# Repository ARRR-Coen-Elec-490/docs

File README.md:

# Documentation Repository

## Table of Contents <!-- omit in toc -->

- [Documentation Repository](#documentation-repository)
    - [Introduction](#introduction)
    - [Repository Structure](#repository-structure)
    - [System Architecture Documentation](#system-architecture-documentation)
    - [Hardware Documentation](#hardware-documentation)
    - [Software Documentation](#software-documentation)
    - [AI Usage Claim](#ai-usage-claim)

## Introduction

This repository serves as the Single Source of Truth (*SSOT*) for Team #23's fulfillment of the COEN/ELEC 490 2026-2027 Capstone Session.  Within this repository, one can find documentation related to every single part of this project, including hardware, software, architecture, and procurement documents.  The documentation found in this repository is updated and maintained regularly to ensure it follows all the appropriate IEEE, IEC, and ISO standards, according to each standards relevancy and availability.

## Repository Structure

```text
docs/
 ┣ ai-usage/                    # AI Prompting Templates and Logs (Empty)
 ┣ hardware-documentation/      # PCB & BOM Documents
 ┃ ┣ abtrs_torso/               # KiCAD PCB, Schematics, and Simulations
 ┃ ┣ abtrs_torso_information/   # PCB Support Documents
 ┃ ┣ bom/                       # Bill of Materials
 ┃ ┣ datasheets/                # Datasheets for all thirs-party components
 ┃ ┣ schematics/                # Auto-Generated Printables
 ┃ ┗ wiring-diagrams/           # System-Level Wiring Information
 ┣ software-documentation/      # Software Business Logic Documents
 ┣ system-architecture/         # Overarching System Architecture Documents
 ┗ user-manuals/                # Operation and Maintenance Documents (Empty)
```

## System Architecture Documentation

The ```system-architecture``` folder contains the black-box and white-box representations of the system, including the interactions betwen the hardware and software layers.  In addition, this folder contains diagrams related to the system operation including flowcharts, activity/sequence diagrams, and entity relationship diagrams.

## Hardware Documentation

The ```hardware-documentation``` folder contains all information related to the PCB and BOM.  Regarding the PCB, schematics, 3D Models, and simulations have been created to demonstrate the design and validation of the board needed for our project.  According to this PCB, a detailed and through BOM was ceated to hold all the components needed for the product being developed.  Furthermore, other 3D models, wiring diagrams, and support documents have been included to illustrate the complete hardware design of this project.

## Software Documentation

The ```software-documentation``` folder contains all the documents related to the various software sub-layers noted in white-box system architecture diagrams.  The contents of this folder expand each layer, providing detailed representations of any software business logic employed in this project.  A combination of flowcharts, activity/sequence diagrams, entity relationship diagrams, and class diagrams can be found for the different layers of the software architecture, to ensure the full illustration of the scope and responsibilities attributed to each software process found in the system.

## AI Usage Claim

In accordance with the policies put forth by both Concordia University and the COEN/ELEC 490 Capstone Committe, AI cannot be used to design or implement any aspects of the capstone project being developed by this team.  Instead, AI may only be used to enhance research or problem-solving processes across the team.  In other words, AI can be leveraged to enhance the toolsets employed by this team, but can in no way directly contribute to the final product of this project.  Failure to comply with these policies will result in grave penalties.  As such, to prevent such a scenario, the ```ai-usage``` folder has been created to contain any and all prompts used throughout the develoment of this project, and will serve as the team's method to demonstrate compliance with the policies discussed above.

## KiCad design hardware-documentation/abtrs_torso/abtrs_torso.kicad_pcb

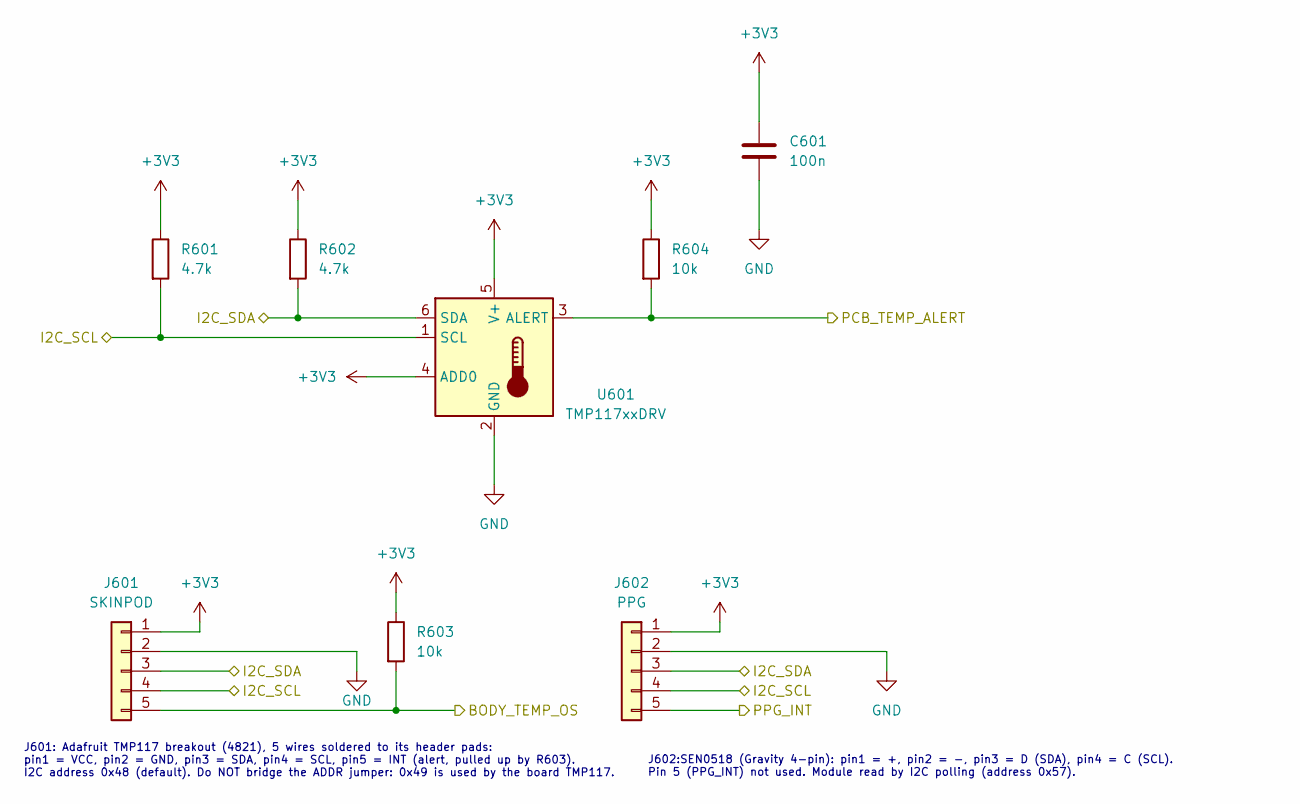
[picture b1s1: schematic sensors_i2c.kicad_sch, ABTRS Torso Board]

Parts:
C601: 100n; C_0603_1608Metric; MPN C0603C104K5RACTU
J601: SKINPOD; JST_PH_S5B-PH-K_1x05_P2.00mm_Horizontal; MPN S5B-PH-K-S
J602: PPG; JST_PH_S5B-PH-K_1x05_P2.00mm_Horizontal; MPN S5B-PH-K-S
R601, R602: 4.7k; R_0603_1608Metric; MPN RC0603FR-074K7L
R603, R604: 10k; R_0603_1608Metric; MPN RC0603FR-0710KL
U601: TMP117xxDRV; WSON-6-1EP_2x2mm_P0.65mm_EP1x1.6mm; MPN TMP117AIDRVR

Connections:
+3V3: C601.1, J601.1, J602.1, R601.1, R602.1, R603.1, R604.1, U601.4 (ADD0), U601.5 (V+); also elsewhere on the board
/BODY_TEMP_OS: J601.5, R603.2; also elsewhere on the board
/I2C_SCL: J601.4, J602.4, R601.2, U601.1 (SCL); also elsewhere on the board
/I2C_SDA: J601.3, J602.3, R602.2, U601.6 (SDA); also elsewhere on the board
/PCB_TEMP_ALERT: R604.2, U601.3 (ALERT); also elsewhere on the board
/PPG_INT: J602.5; also elsewhere on the board
GND: C601.2, J601.2, J602.2, U601.2 (GND); also elsewhere on the board

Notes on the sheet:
J602:SEN0518 (Gravity 4-pin): pin1 = +, pin2 = -, pin3 = D (SDA), pin4 = C (SCL). Pin 5 (PPG_INT) not used. Module read by I2C polling (address 0x57).
J601: Adafruit TMP117 breakout (4821), 5 wires soldered to its header pads: pin1 = VCC, pin2 = GND, pin3 = SDA, pin4 = SCL, pin5 = INT (alert, pulled up by R603). I2C address 0x48 (default). Do NOT bridge the ADDR jumper: 0x49 is used by the board TMP117.

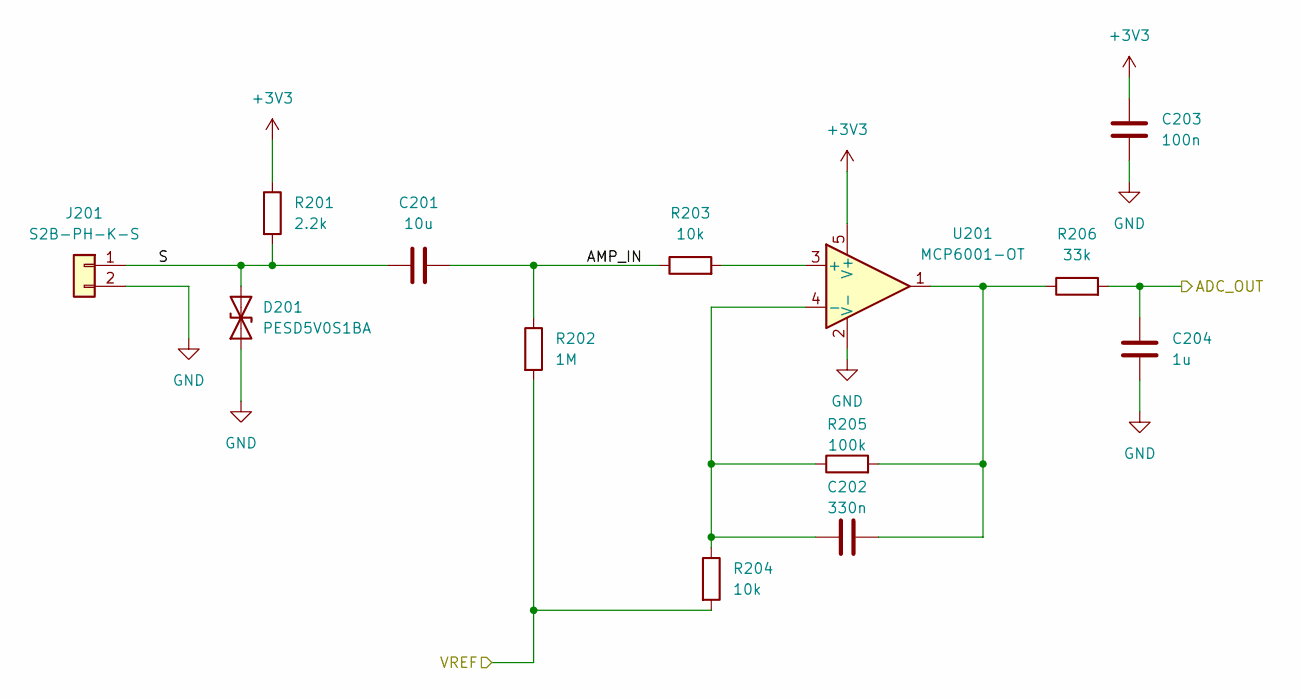
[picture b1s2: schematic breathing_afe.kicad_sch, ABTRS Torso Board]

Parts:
C201: 10u; C_0603_1608Metric; MPN CL10A106KP8NNNC
C202: 330n; C_0603_1608Metric; MPN CL10B334KO8NNNC
C203: 100n; C_0603_1608Metric; MPN C0603C104K5RACTU
C204: 1u; C_0603_1608Metric; MPN CC0603KPX5R9BB105
D201: PESD5V0S1BA; D_SOD-323; MPN PESD5V0S1BA,115
J201: S2B-PH-K-S; JST_PH_S2B-PH-K_1x02_P2.00mm_Horizontal; MPN S2B-PH-K-S
R201: 2.2k; R_0603_1608Metric; MPN AC0603FR-072K2L
R202: 1M; R_0603_1608Metric; MPN RC0603FR-071ML
R203, R204: 10k; R_0603_1608Metric; MPN RC0603FR-0710KL
R205: 100k; R_0603_1608Metric; MPN AC0603FR-07100KL
R206: 33k; R_0603_1608Metric; MPN RC0603FR-0733KL
U201: MCP6001-OT; SOT-23-5; MPN MCP6001T-I/OT

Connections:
+3V3: C203.1, R201.1, U201.5 (V+); also elsewhere on the board
/CHEST/AMP_IN: C201.2, R202.1, R203.1
/CHEST/S: C201.1, D201.2 (A2), J201.1, R201.2
/CHEST_ADC: C204.1, R206.2; also elsewhere on the board
/VREF: R202.2, R204.2; also elsewhere on the board
GND: C203.2, C204.2, D201.1 (A1), J201.2, U201.2 (V-); also elsewhere on the board
unnamed: C202.2, R205.2, R206.1, U201.1
unnamed: R203.2, U201.3 (+)
unnamed: C202.1, R204.1, R205.1, U201.4 (-)

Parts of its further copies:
C301: 10u; C_0603_1608Metric; MPN CL10A106KP8NNNC
C302: 330n; C_0603_1608Metric; MPN CL10B334KO8NNNC
C303: 100n; C_0603_1608Metric; MPN C0603C104K5RACTU
C304: 1u; C_0603_1608Metric; MPN CC0603KPX5R9BB105
D301: PESD5V0S1BA; D_SOD-323; MPN PESD5V0S1BA,115
J301: S2B-PH-K-S; JST_PH_S2B-PH-K_1x02_P2.00mm_Horizontal; MPN S2B-PH-K-S
R301: 2.2k; R_0603_1608Metric; MPN AC0603FR-072K2L
R302: 1M; R_0603_1608Metric; MPN RC0603FR-071ML
R303, R304: 10k; R_0603_1608Metric; MPN RC0603FR-0710KL
R305: 100k; R_0603_1608Metric; MPN AC0603FR-07100KL
R306: 33k; R_0603_1608Metric; MPN RC0603FR-0733KL
U301: MCP6001-OT; SOT-23-5; MPN MCP6001T-I/OT

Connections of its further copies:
+3V3: C303.1, R301.1, U301.5 (V+); also elsewhere on the board
/ABD/AMP_IN: C301.2, R302.1, R303.1
/ABD/S: C301.1, D301.2 (A2), J301.1, R301.2
/ABD_ADC: C304.1, R306.2; also elsewhere on the board
/VREF: R302.2, R304.2; also elsewhere on the board
GND: C303.2, C304.2, D301.1 (A1), J301.2, U301.2 (V-); also elsewhere on the board
unnamed: C302.2, R305.2, R306.1, U301.1
unnamed: R303.2, U301.3 (+)
unnamed: C302.1, R304.1, R305.1, U301.4 (-)

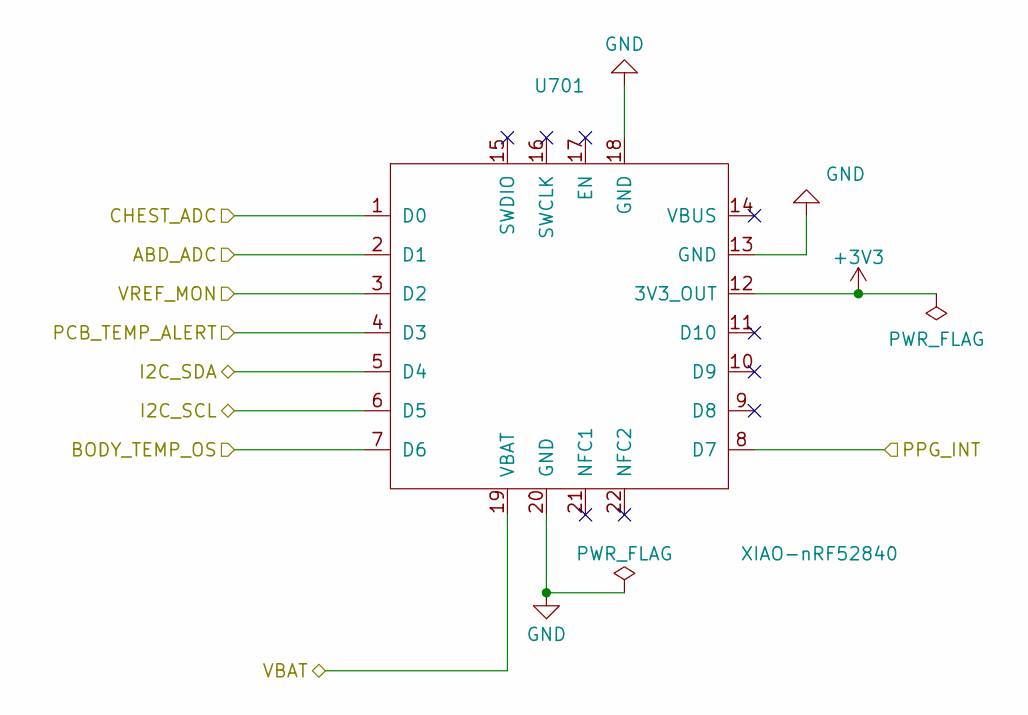
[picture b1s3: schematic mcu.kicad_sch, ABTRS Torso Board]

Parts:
U701: XIAO-nRF52840; XIAO-nRF52840-SMD; MPN 102010448

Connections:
+3V3: U701.12 (3V3_OUT); also elsewhere on the board
/ABD_ADC: U701.2 (D1); also elsewhere on the board
/BODY_TEMP_OS: U701.7 (D6); also elsewhere on the board
/CHEST_ADC: U701.1 (D0); also elsewhere on the board
/I2C_SCL: U701.6 (D5); also elsewhere on the board
/I2C_SDA: U701.5 (D4); also elsewhere on the board
/PCB_TEMP_ALERT: U701.4 (D3); also elsewhere on the board
/PPG_INT: U701.8 (D7); also elsewhere on the board
/VBAT: U701.19 (VBAT); also elsewhere on the board
/VREF: U701.3 (D2); also elsewhere on the board
GND: U701.13 (GND), U701.18 (GND), U701.20 (GND); also elsewhere on the board

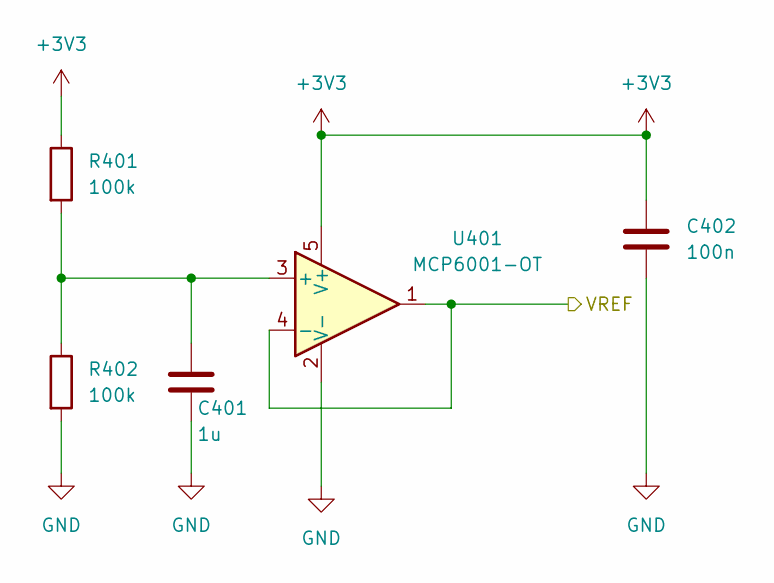
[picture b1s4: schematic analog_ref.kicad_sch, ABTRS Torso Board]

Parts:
C401: 1u; C_0603_1608Metric; MPN CC0603KPX5R9BB105
C402: 100n; C_0603_1608Metric; MPN C0603C104K5RACTU
R401, R402: 100k; R_0603_1608Metric; MPN AC0603FR-07100KL
U401: MCP6001-OT; SOT-23-5; MPN MCP6001T-I/OT

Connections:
+3V3: C402.1, R401.1, U401.5 (V+); also elsewhere on the board
/VREF: U401.1, U401.4 (-); also elsewhere on the board
GND: C401.2, C402.2, R402.2, U401.2 (V-); also elsewhere on the board
unnamed: C401.1, R401.2, R402.1, U401.3 (+)

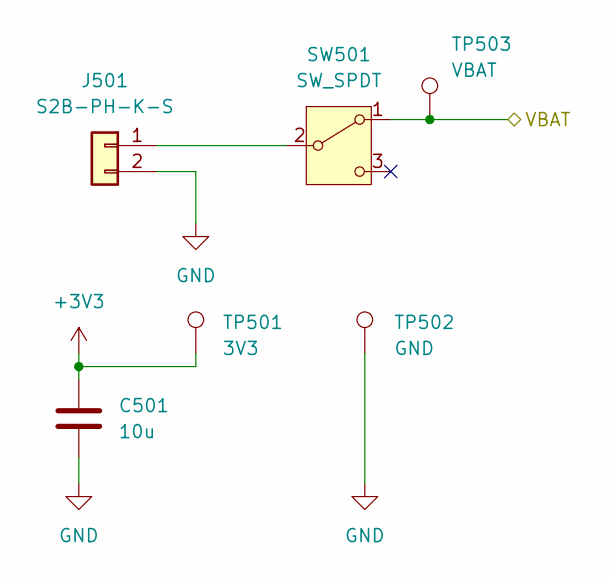
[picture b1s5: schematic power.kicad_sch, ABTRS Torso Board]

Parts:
C501: 10u; C_0603_1608Metric; MPN CL10A106KP8NNNC
J501: S2B-PH-K-S; JST_PH_S2B-PH-K_1x02_P2.00mm_Horizontal; MPN S2B-PH-K-S
SW501: SW_SPDT; SW_SPDT_CK_JS102011SAQN; MPN JS102011SAQN
TP501: 3V3; TestPoint_Pad_D1.5mm
TP502: GND; TestPoint_Pad_D1.5mm
TP503: VBAT; TestPoint_Pad_D1.5mm

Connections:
+3V3: C501.1, TP501.1 (1_1); also elsewhere on the board
/VBAT: SW501.1 (A), TP503.1 (1_1); also elsewhere on the board
GND: C501.2, J501.2, TP502.1 (1_1); also elsewhere on the board
unnamed: J501.1, SW501.2 (B)

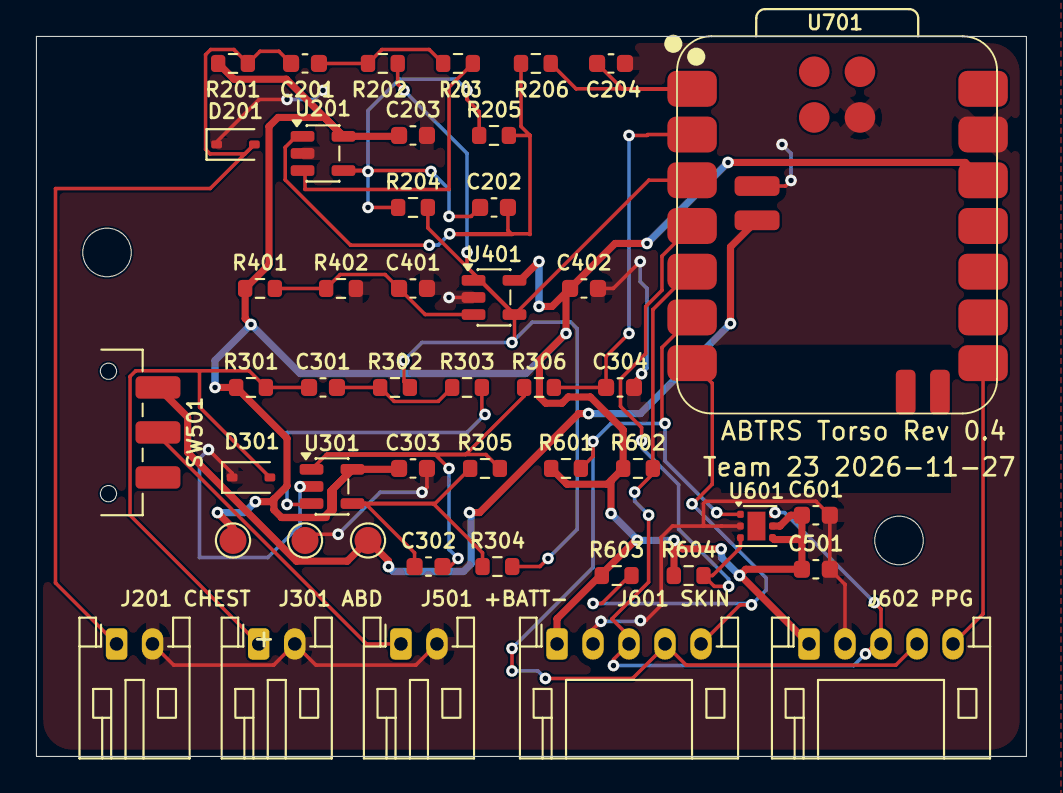
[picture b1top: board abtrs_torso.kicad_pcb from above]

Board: 2 copper layers, 55.0 x 40.0 mm, 48 parts (0 on the bottom side), 23 nets.

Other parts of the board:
H1, H2: MountingHole_2.7mm_M2.5

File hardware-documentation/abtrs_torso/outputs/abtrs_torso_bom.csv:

"Reference","Qty","Value","Footprint","Datasheet","#","Manufacturer","MPN","Supplier","Supplier P/N"
"SW501","1","SW_SPDT","Button_Switch_SMD:SW_SPDT_CK_JS102011SAQN","https://www.littelfuse.com/assetdocs/littelfuse-c-k-slide-js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","1","C&K","JS102011SAQN","DigiKey","401-1999-1-ND"
"C201,C301,C501","3","10u","Capacitor_SMD:C_0603_1608Metric","https://mm.digikey.com/Volume0/opasdata/d220001/medias/docus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","2","Samsung Electro-Mechanics","CL10A106KP8NNNC","DigiKey","1276-1192-1-ND"
"C202,C302","2","330n","Capacitor_SMD:C_0603_1608Metric","https://mm.digikey.com/Volume0/opasdata/d220001/medias/docus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","3","Samsung Electro-Mechanics","CL10B334KO8NNNC","DigiKey","1276-2048-1-ND"
"C203,C303,C402,C601","4","100n","Capacitor_SMD:C_0603_1608Metric","https://yageogroup.com/content/datasheet/asset/file/KEM_C100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","4","KEMET","C0603C104K5RACTU","DigiKey","399-C0603C104K5RACTUCT-ND"
"C204,C304,C401","3","1u","Capacitor_SMD:C_0603_1608Metric","https://yageogroup.com/content/datasheet/asset/file/UPY-GPHC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","5","Yageo","CC0603KPX5R9BB105","DigiKey","13-CC0603KPX5R9BB105CT-ND"
"J501","1","LiPo","Connector_JST:JST_PH_B2B-PH-K_1x02_P2.00mm_Vertical","https://www.jst-mfg.com/product/pdf/eng/ePH.pdf","6","JST","B2B-PH-K-S","DigiKey","455-1704-ND"
"J201,J301","2","Cord","Connector_JST:JST_PH_S2B-PH-K_1x02_P2.00mm_Horizontal","https://www.jst-mfg.com/product/pdf/eng/ePH.pdf","7","JST","S2B-PH-K-S","DigiKey","455-1719-ND"
"J601","1","SKINPOD","Connector_JST:JST_PH_S5B-PH-K_1x05_P2.00mm_Horizontal","https://www.jst-mfg.com/product/pdf/eng/ePH.pdf","8","JST","S5B-PH-K-S","DigiKey","455-1722-ND"
"J602","1","PPG","Connector_JST:JST_PH_S5B-PH-K_1x05_P2.00mm_Horizontal","https://www.jst-mfg.com/product/pdf/eng/ePH.pdf","9","JST","S5B-PH-K-S","DigiKey","455-1722-ND"
"D201,D301","2","PESD5V0S1BA","Diode_SMD:D_SOD-323","https://assets.nexperia.com/documents/data-sheet/PESD5V0S1BA.pdf","10","Nexperia","PESD5V0S1BA,115","DigiKey","1727-PESD5V0S1BA,115CT-ND"
"U601","1","TMP117xxDRV","Package_SON:WSON-6-1EP_2x2mm_P0.65mm_EP1x1.6mm","https://www.ti.com/lit/ds/symlink/tmp117.pdf","11","Texas Instruments","TMP117AIDRVR","DigiKey","296-51834-1-ND"
"U201,U301,U401","3","MCP6001-OT","Package_TO_SOT_SMD:SOT-23-5","https://ww1.microchip.com/downloads/en/DeviceDoc/MCP6001-1R-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","12","Microchip Technology","MCP6001T-I/OT","DigiKey","MCP6001T-I/OTCT-ND"
"R201,R301","2","2.2k","Resistor_SMD:R_0603_1608Metric","https://yageogroup.com/content/datasheet/asset/file/PYU-AC_5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","13","Yageo","AC0603FR-072K2L","DigiKey","311-2.2KLDCT-ND"
"R202,R302","2","1M","Resistor_SMD:R_0603_1608Metric","https://yageogroup.com/content/datasheet/asset/file/PYU-RC_G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","14","Yageo","RC0603FR-071ML","DigiKey","311-1.00MHRCT-ND"
"R203,R204,R303,R304,R603,R604","6","10k","Resistor_SMD:R_0603_1608Metric","https://yageogroup.com/content/datasheet/asset/file/PYU-RC_G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","15","Yageo","RC0603FR-0710KL","DigiKey","311-10.0KHRCT-ND"
"R205,R305,R401,R402","4","100k","Resistor_SMD:R_0603_1608Metric","https://yageogroup.com/content/datasheet/asset/file/PYU-AC_5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","16","Yageo","AC0603FR-07100KL","DigiKey","311-100KLDCT-ND"
"R206,R306","2","33k","Resistor_SMD:R_0603_1608Metric","https://yageogroup.com/content/datasheet/asset/file/PYU-RC_G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","17","Yageo","RC0603FR-0733KL","DigiKey","311-33.0KHRCT-ND"
"R601,R602","2","4.7k","Resistor_SMD:R_0603_1608Metric","https://yageogroup.com/content/datasheet/asset/file/PYU-RC_G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","18","Yageo","RC0603FR-074K7L","DigiKey","311-4.70KHRCT-ND"
"U701","1","XIAO-nRF52840","Seeed_Studio_XIAO_Series:XIAO-nRF52840-SMD","https://files.seeedstudio.com/Bazaar/product_pdf/102010448.pdf","19","Seeed Technology","102010448","DigiKey","1597-102010448-ND"
